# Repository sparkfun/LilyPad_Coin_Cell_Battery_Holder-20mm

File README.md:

**NOTE:** *This product has been retired from our catalog. If you are looking for more up-to-date info, please check out some of these resources to see how other users are still hacking and improving on this product.*
* *[SparkFun Forum](https://forum.sparkfun.com/)*
* *[IRC Channel](https://www.sparkfun.com/news/263)*

SparkFun LilyPad Coin Cell Battery Holder-20mm
===============================================

[*SparkFun LilyPad Coin Cell Battery Holder-20mm (DEV-10730)*](https://www.sparkfun.com/products/10730)

If you’re looking for a simple way to add a battery to your LilyPad project, the LilyPad Coin Cell Battery Holder might do the trick. It’s a simple board 
which holds a 20mm coin cell battery (such as a CR2032) and gives you 4 connection points (two positive and two negative) for sewing into your project.

Repository Contents
-------------------
* **/Hardware** - All Eagle design files (.brd, .sch)

License Information
-------------------
The hardware is released under [Creative Commons ShareAlike 4.0 International](https://creativecommons.org/licenses/by-sa/4.0/).

Distributed as-is; no warranty is given.

_The LilyPad Coin Cell Battery Holder is a design conceived by Felicia Williams of Boulder, Colorado._ 
_Also, a portion of this sale is given back to Dr. Leah Buechley for continued development and education of e-textiles._

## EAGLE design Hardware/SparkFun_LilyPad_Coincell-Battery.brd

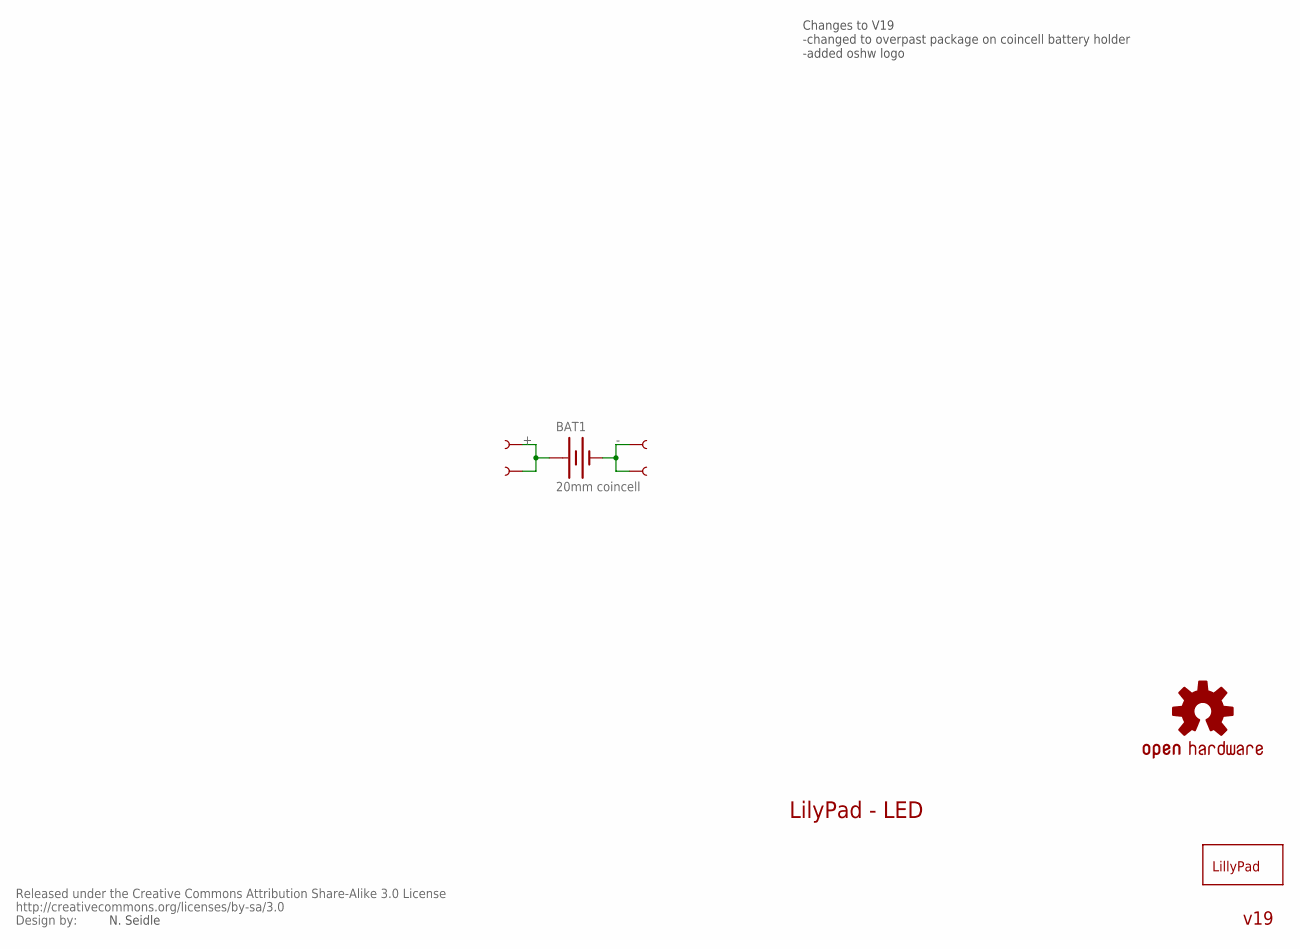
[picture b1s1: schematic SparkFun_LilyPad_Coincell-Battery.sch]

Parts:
BAT1: 20mm coincell; BATTCON_20MM_4LEGS_OVERPASTE
U$1, U$2, U$3, U$4: SEWTAP6; PETAL-SMALL-2SIDE
U$5: LOGO-LPLP; LOGO-LILYPAD
U$6: CREATIVE_COMMONS
U$7: OSHW-LOGOS; OSHW-LOGO-S

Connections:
+: BAT1.1 (+), U$2.1, U$4.1
-: BAT1.2 (-), U$1.1, U$3.1

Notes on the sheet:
LilyPad - LED
N. Seidle
Changes to V19 -changed to overpast package on coincell battery holder -added oshw logo
v19

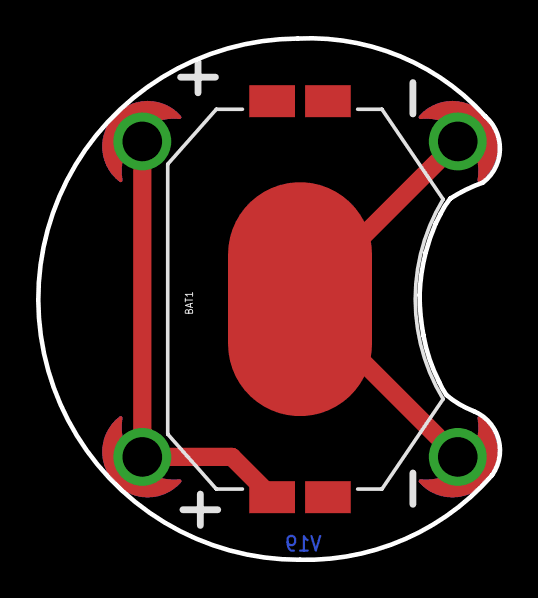
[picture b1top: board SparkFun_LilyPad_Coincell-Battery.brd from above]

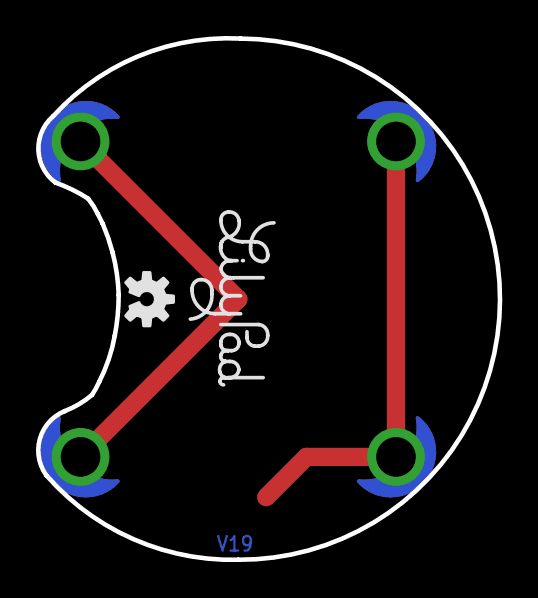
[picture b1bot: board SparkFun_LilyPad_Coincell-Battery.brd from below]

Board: 2 copper layers, 25.7 x 29.0 mm, 8 parts (2 on the bottom side), 2 nets.

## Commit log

2015-02-19 Adding README info, hardware files

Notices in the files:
parts and their libraries:
SparkFun: Released under the Creative Commons Attribution Share-Alike 3.0 License
SparkFun: http://creativecommons.org/licenses/by-sa/3.0
SparkFun-Electromechanical: Licensing: CC v3.0 Share-Alike You are welcome to use this library for commercial purposes.
